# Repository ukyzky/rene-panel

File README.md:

# rene-panel

Make Noise René (Classic) Mechanical Keyswitch DIY Panel

## v1.0 image

## Bom

- Cherry MX keyswitch x18
- keycap for Cherry MX x18
- 2.54mm wirehousing header socket 1 row 10 pin for smd/smt (first pin is left sided) x2

(or you can use THT header socket and bend the pins)

## Status

### v1.0

renepanel01a.zip

Production completed and works good.

There is an error in the position of some holes.

But the error in the position is a little, so assembly successful.

### v1.1

renepanel01a_v1.1.zip

Production not yet started.

Improved version of v1.0 the error in the position.

So it maybe works fine.

## Notes

The panel has the holes of LED for keyswitch.

The holes aren't connected to anywhere.

If you'd like to light up the keyswitches, please DIY external circuit, wiring etc.

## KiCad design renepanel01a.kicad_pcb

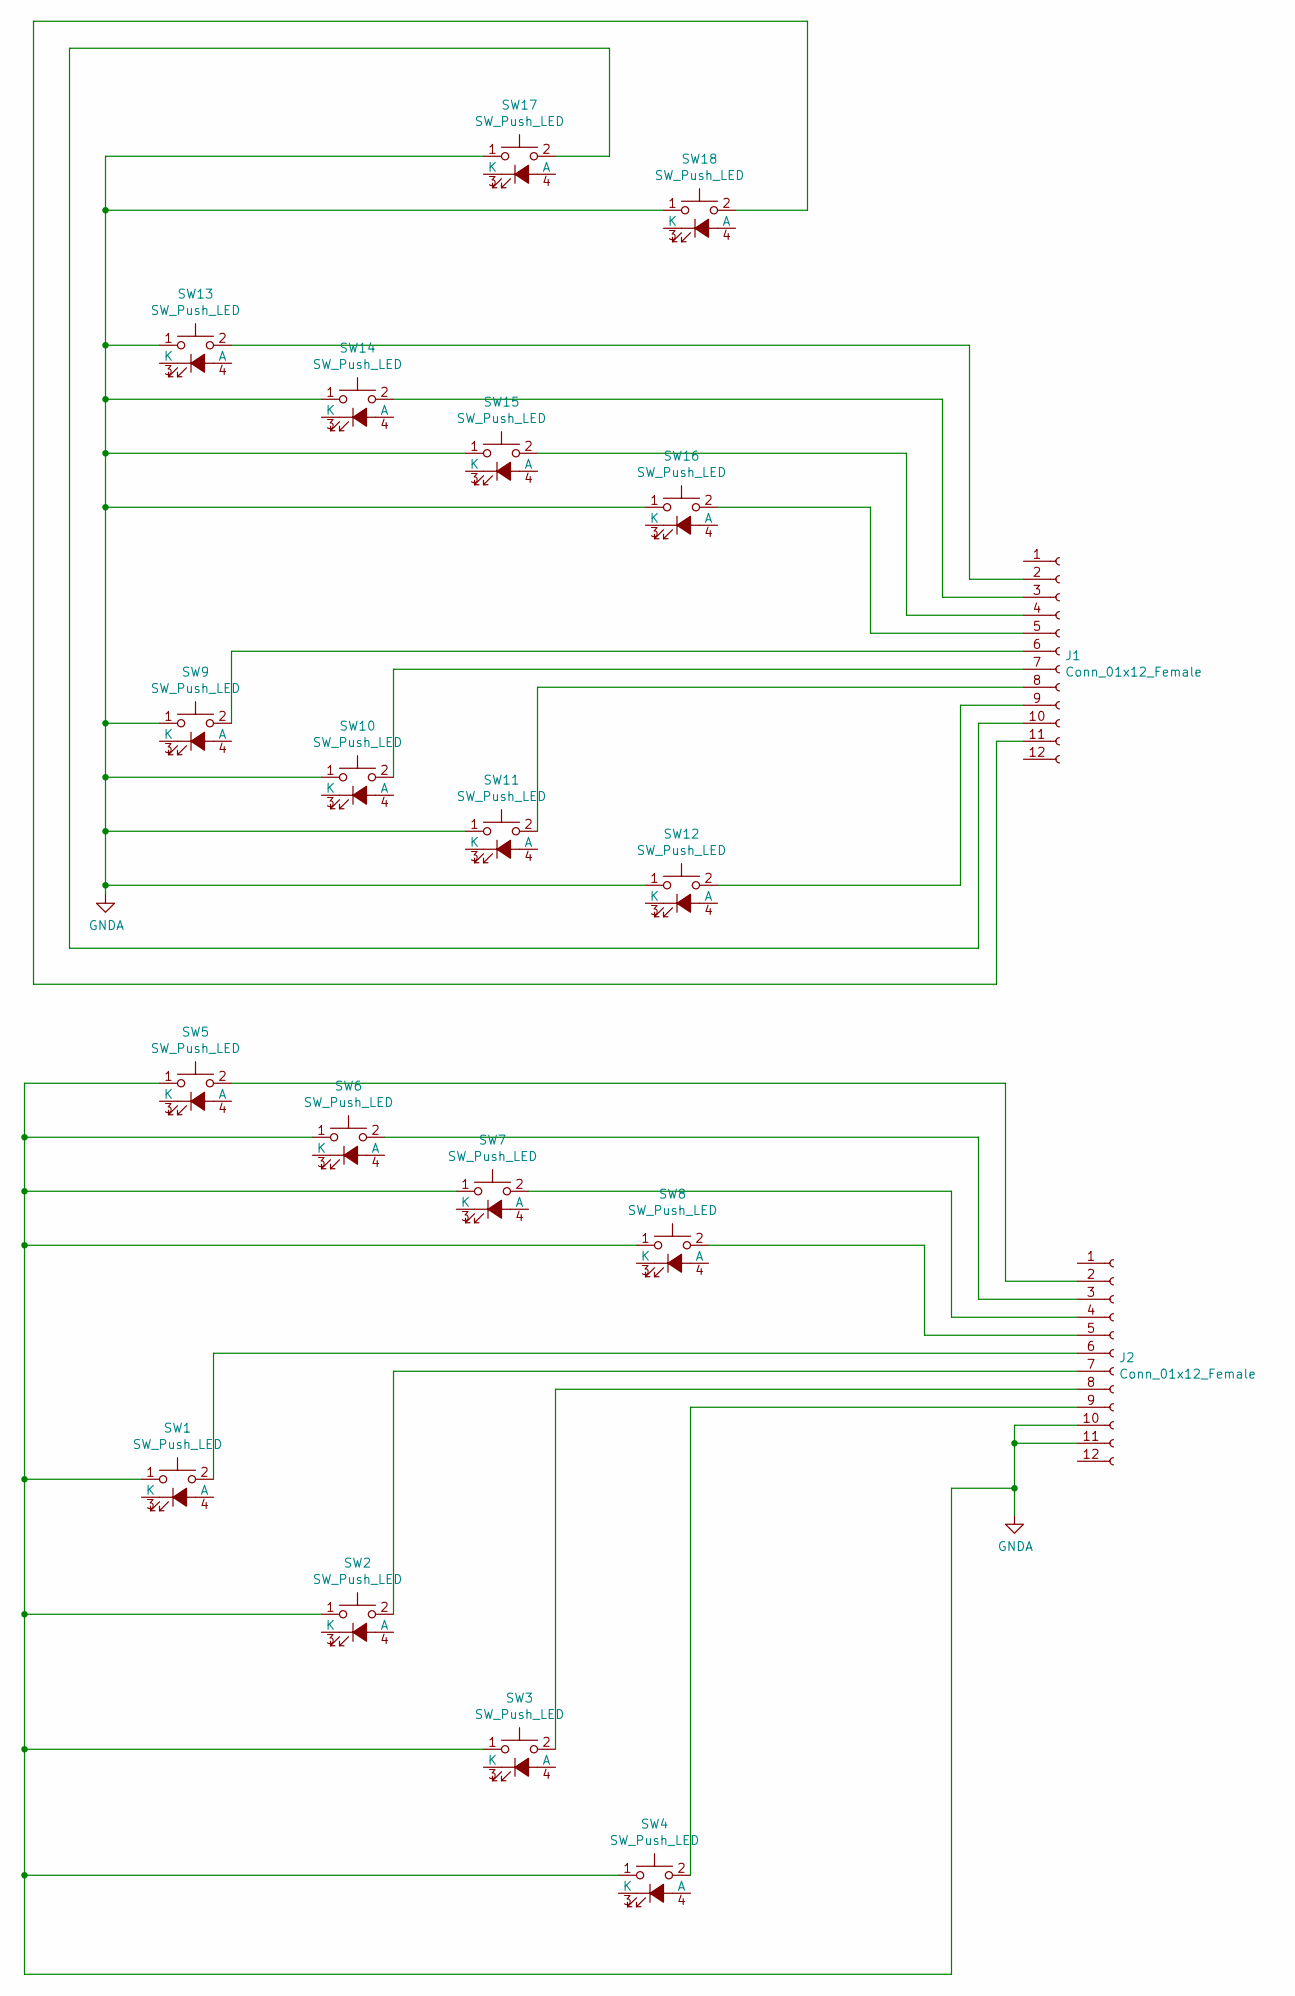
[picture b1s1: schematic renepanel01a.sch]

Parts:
J1, J2: Conn_01x12_Female; PinSocket_1x12_P2.54mm_Vertical_SMD_Pin1Right
SW1, SW2, SW3, SW4, SW5, SW6, SW7, SW8, SW9, SW10, SW11, SW12, SW13, SW14, SW15, SW16, SW17, SW18: SW_Push_LED; CherryMX_1.00u_LED

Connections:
GNDA: J2.10, J2.11, SW1.1, SW2.1, SW3.1, SW4.1, SW5.1, SW6.1, SW7.1, SW8.1, SW9.1, SW10.1, SW11.1, SW12.1, SW13.1, SW14.1, SW15.1, SW16.1, SW17.1, SW18.1
unnamed: J1.2, SW13.2
unnamed: J1.3, SW14.2
unnamed: J1.4, SW15.2
unnamed: J1.5, SW16.2
unnamed: J1.6, SW9.2
unnamed: J1.7, SW10.2
unnamed: J1.8, SW11.2
unnamed: J1.9, SW12.2
unnamed: J1.10, SW17.2
unnamed: J1.11, SW18.2
unnamed: J2.2, SW5.2
unnamed: J2.3, SW6.2
unnamed: J2.4, SW7.2
unnamed: J2.5, SW8.2
unnamed: J2.6, SW1.2
unnamed: J2.7, SW2.2
unnamed: J2.8, SW3.2
unnamed: J2.9, SW4.2

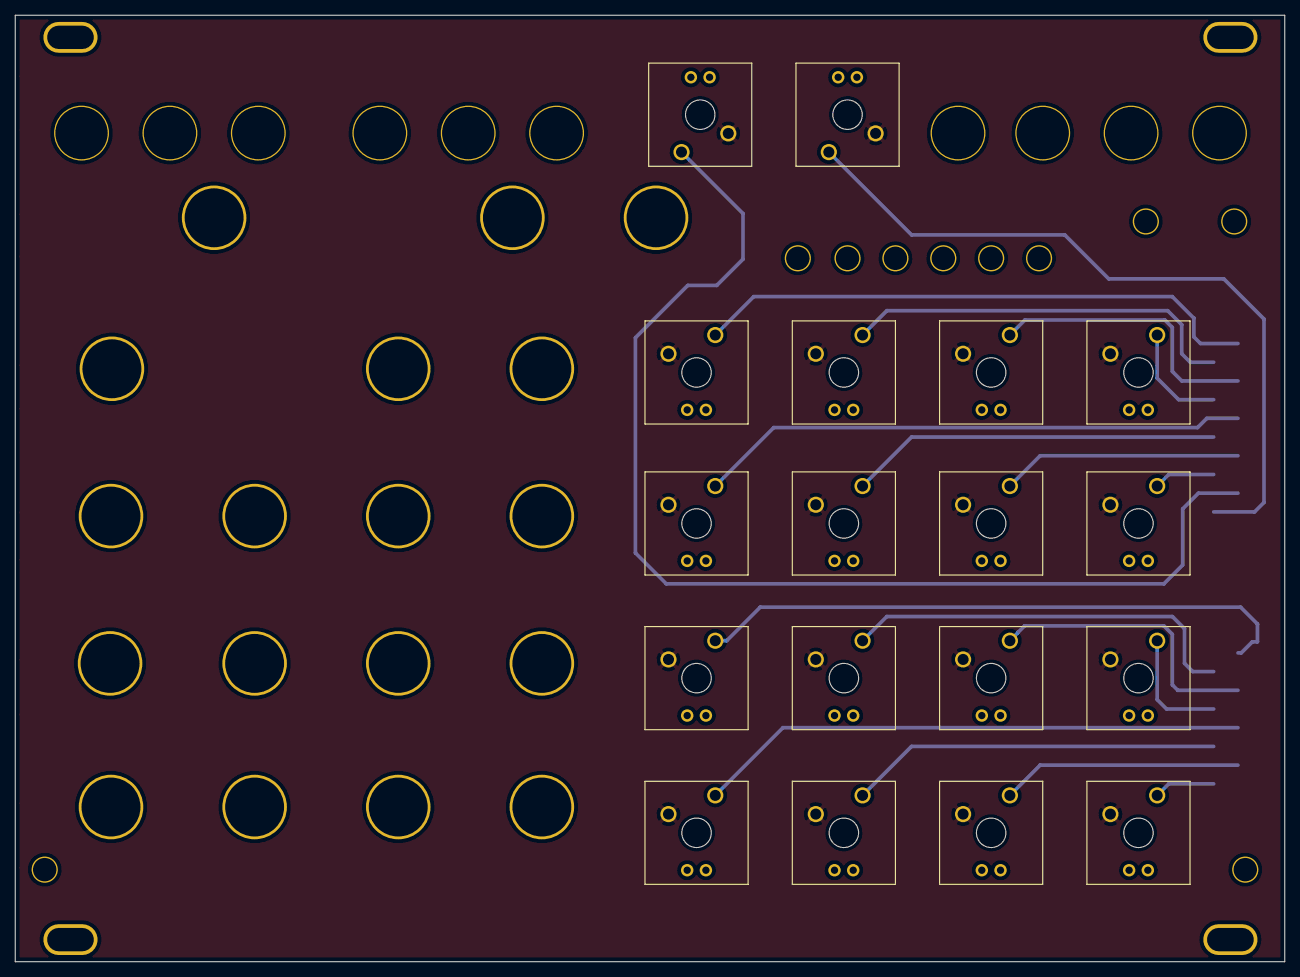
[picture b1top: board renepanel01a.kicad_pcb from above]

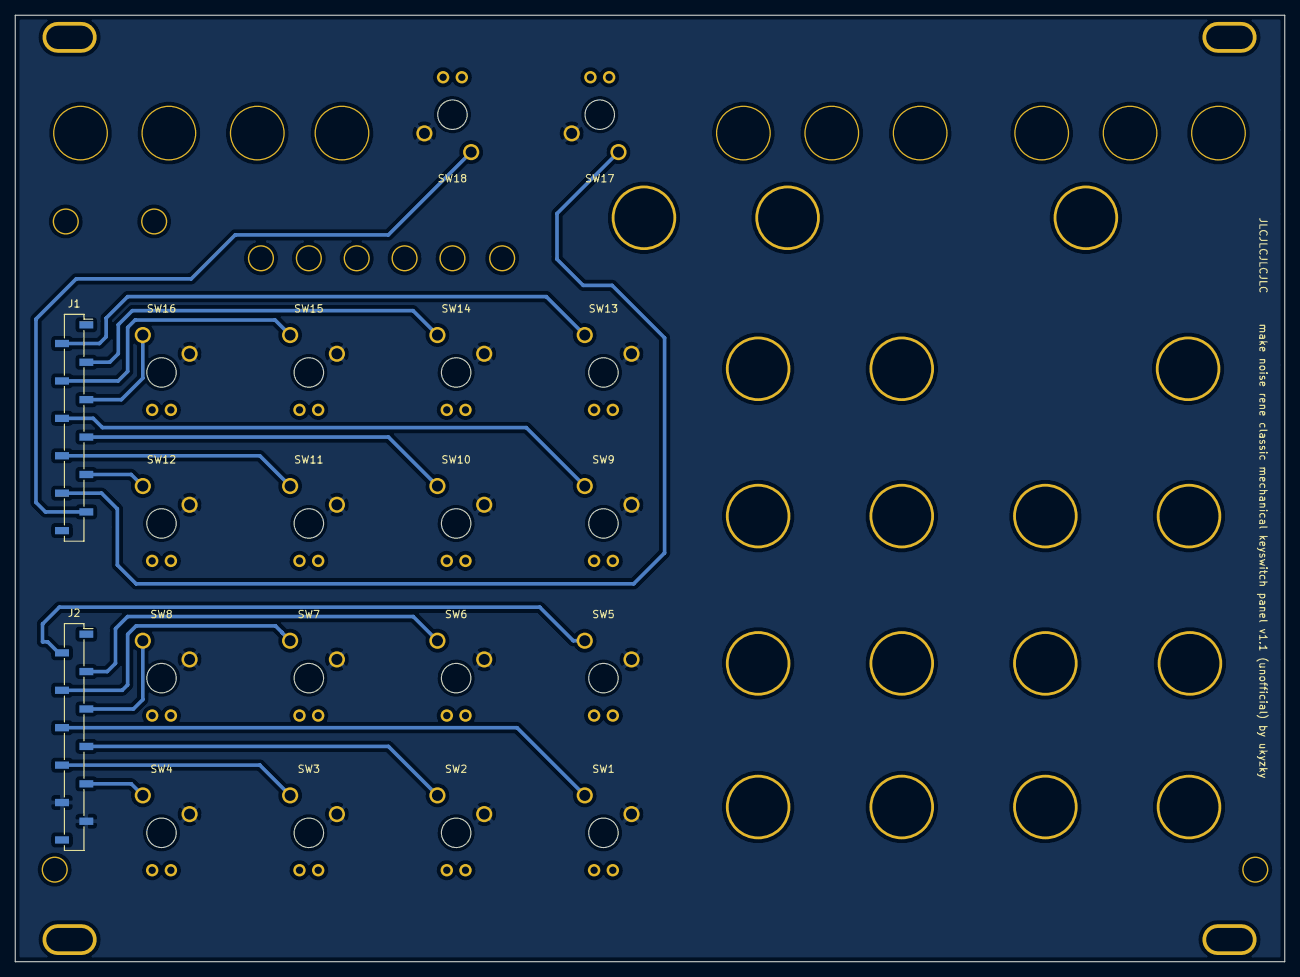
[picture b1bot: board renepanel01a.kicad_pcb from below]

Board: 2 copper layers, 172.4 x 128.5 mm, 20 parts (2 on the bottom side), 19 nets.

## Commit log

2021-08-22 Add panel.
2021-08-22 Add v1.1 panel.
2021-08-22 Add images.
